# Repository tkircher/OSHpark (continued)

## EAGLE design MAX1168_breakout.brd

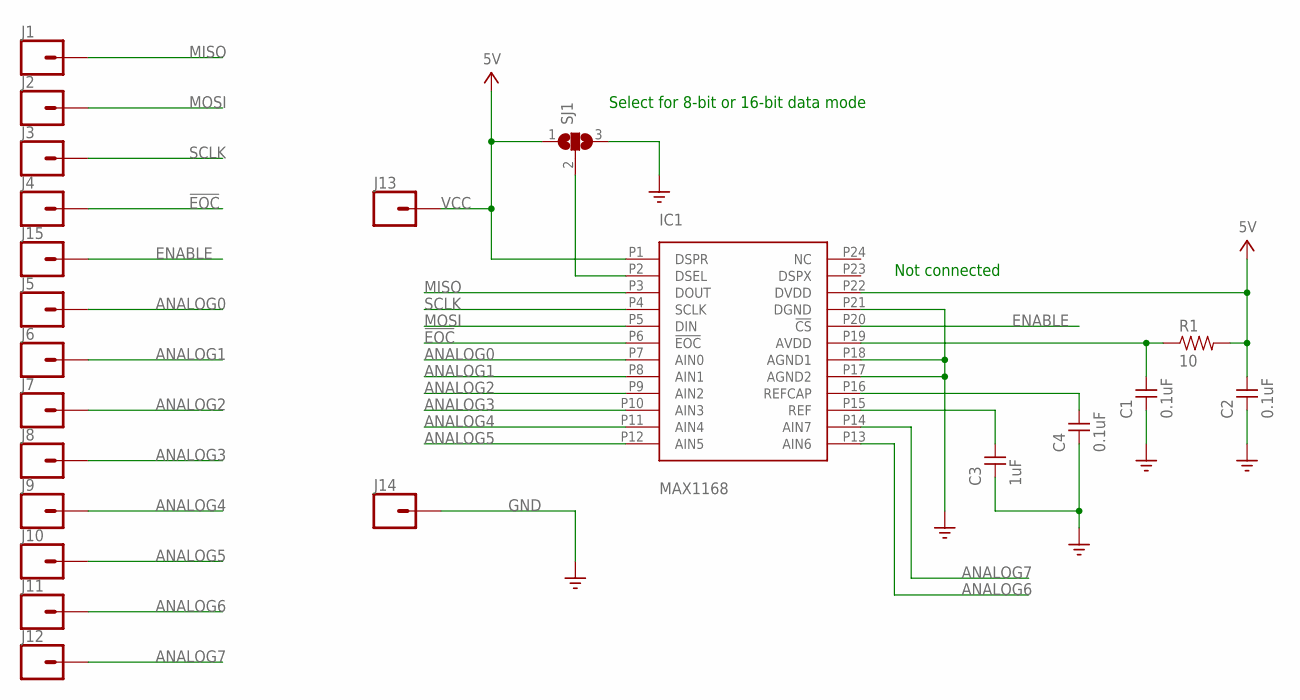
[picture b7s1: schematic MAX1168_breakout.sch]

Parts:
C1, C2, C4: 0.1uF; 0805
C3: 1uF; 0805
IC1: MAX1168; QSOP-24
J1, J2, J3, J4, J5, J6, J7, J8, J9, J10, J11, J12, J13, J14, J15: CONN_01PTH_NO_SILK_YES_STOP; 1X01_NO_SILK
R1: 10; 0805
SJ1: SJ2W; SJ_2

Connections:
!EOC: IC1.P6 (!EOC), J4.1
ANALOG0: IC1.P7 (AIN0), J5.1
ANALOG1: IC1.P8 (AIN1), J6.1
ANALOG2: IC1.P9 (AIN2), J7.1
ANALOG3: IC1.P10 (AIN3), J8.1
ANALOG4: IC1.P11 (AIN4), J9.1
ANALOG5: IC1.P12 (AIN5), J10.1
ANALOG6: IC1.P13 (AIN6), J11.1
ANALOG7: IC1.P14 (AIN7), J12.1
ENABLE: IC1.P20 (!CS), J15.1
GND: C1.1, C2.1, C3.1, C4.1, IC1.P17 (AGND2), IC1.P18 (AGND1), IC1.P21 (DGND), J14.1, SJ1.3
MISO: IC1.P3 (DOUT), J1.1
MOSI: IC1.P5 (DIN), J2.1
unnamed: IC1.P2 (DSEL), SJ1.2
unnamed: C3.2, IC1.P15 (REF)
unnamed: C1.2, IC1.P19 (AVDD), R1.1
unnamed: C4.2, IC1.P16 (REFCAP)
SCLK: IC1.P4 (SCLK), J3.1
VCC: C2.2, IC1.P1 (DSPR), IC1.P22 (DVDD), J13.1, R1.2, SJ1.1

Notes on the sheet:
Select for 8-bit or 16-bit data mode
Not connected

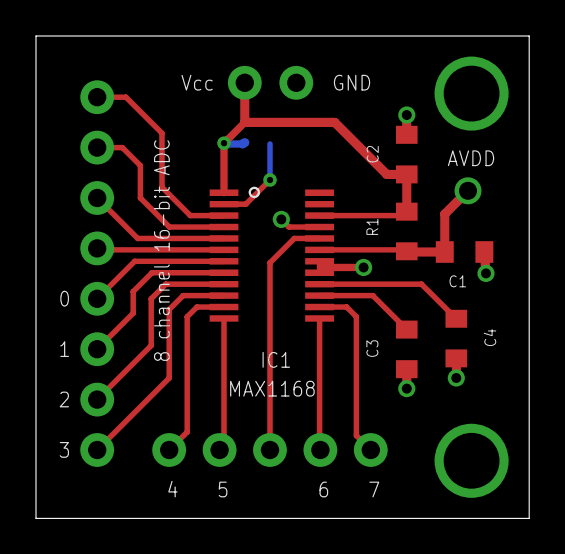
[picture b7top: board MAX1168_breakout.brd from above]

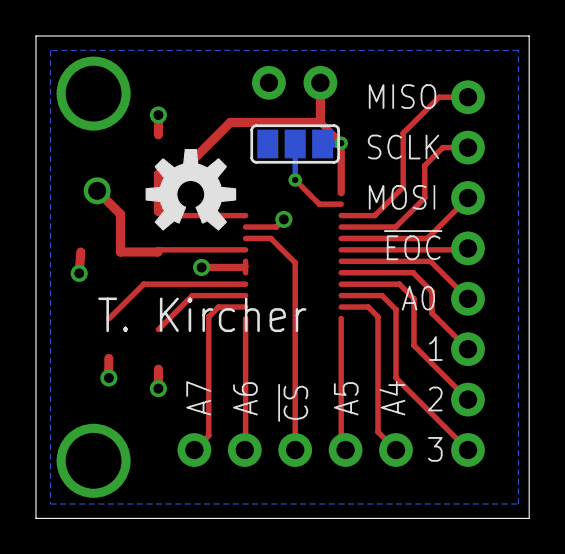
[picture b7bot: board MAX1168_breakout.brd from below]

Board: 2 copper layers, 27.4 x 26.8 mm, 23 parts (2 on the bottom side), 19 nets.

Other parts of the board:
U$9: OSHW-LOGO-M

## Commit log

2018-04-26 Add files via upload
    Initial upload of the AD5933 and MAX1168 breakout boards
2018-04-26 Add files via upload
    Added PDF versions of schematics for the AD5933 and MAX1168 breakout boards
2018-04-26 Add files via upload
    Gerber files for the AD5933 and MAX1168 breakout boards
2018-04-26 Add files via upload
    Impedance analyzer files
2018-04-26 Add files via upload
    Sensor node files
2018-11-15 Added linear scale CAD and gerber files
2018-11-15 Added geiger counter design files
2018-11-30 Part value modification
2018-12-12 Preliminary firmware for geiger counter
    Tested, works. More features later.
